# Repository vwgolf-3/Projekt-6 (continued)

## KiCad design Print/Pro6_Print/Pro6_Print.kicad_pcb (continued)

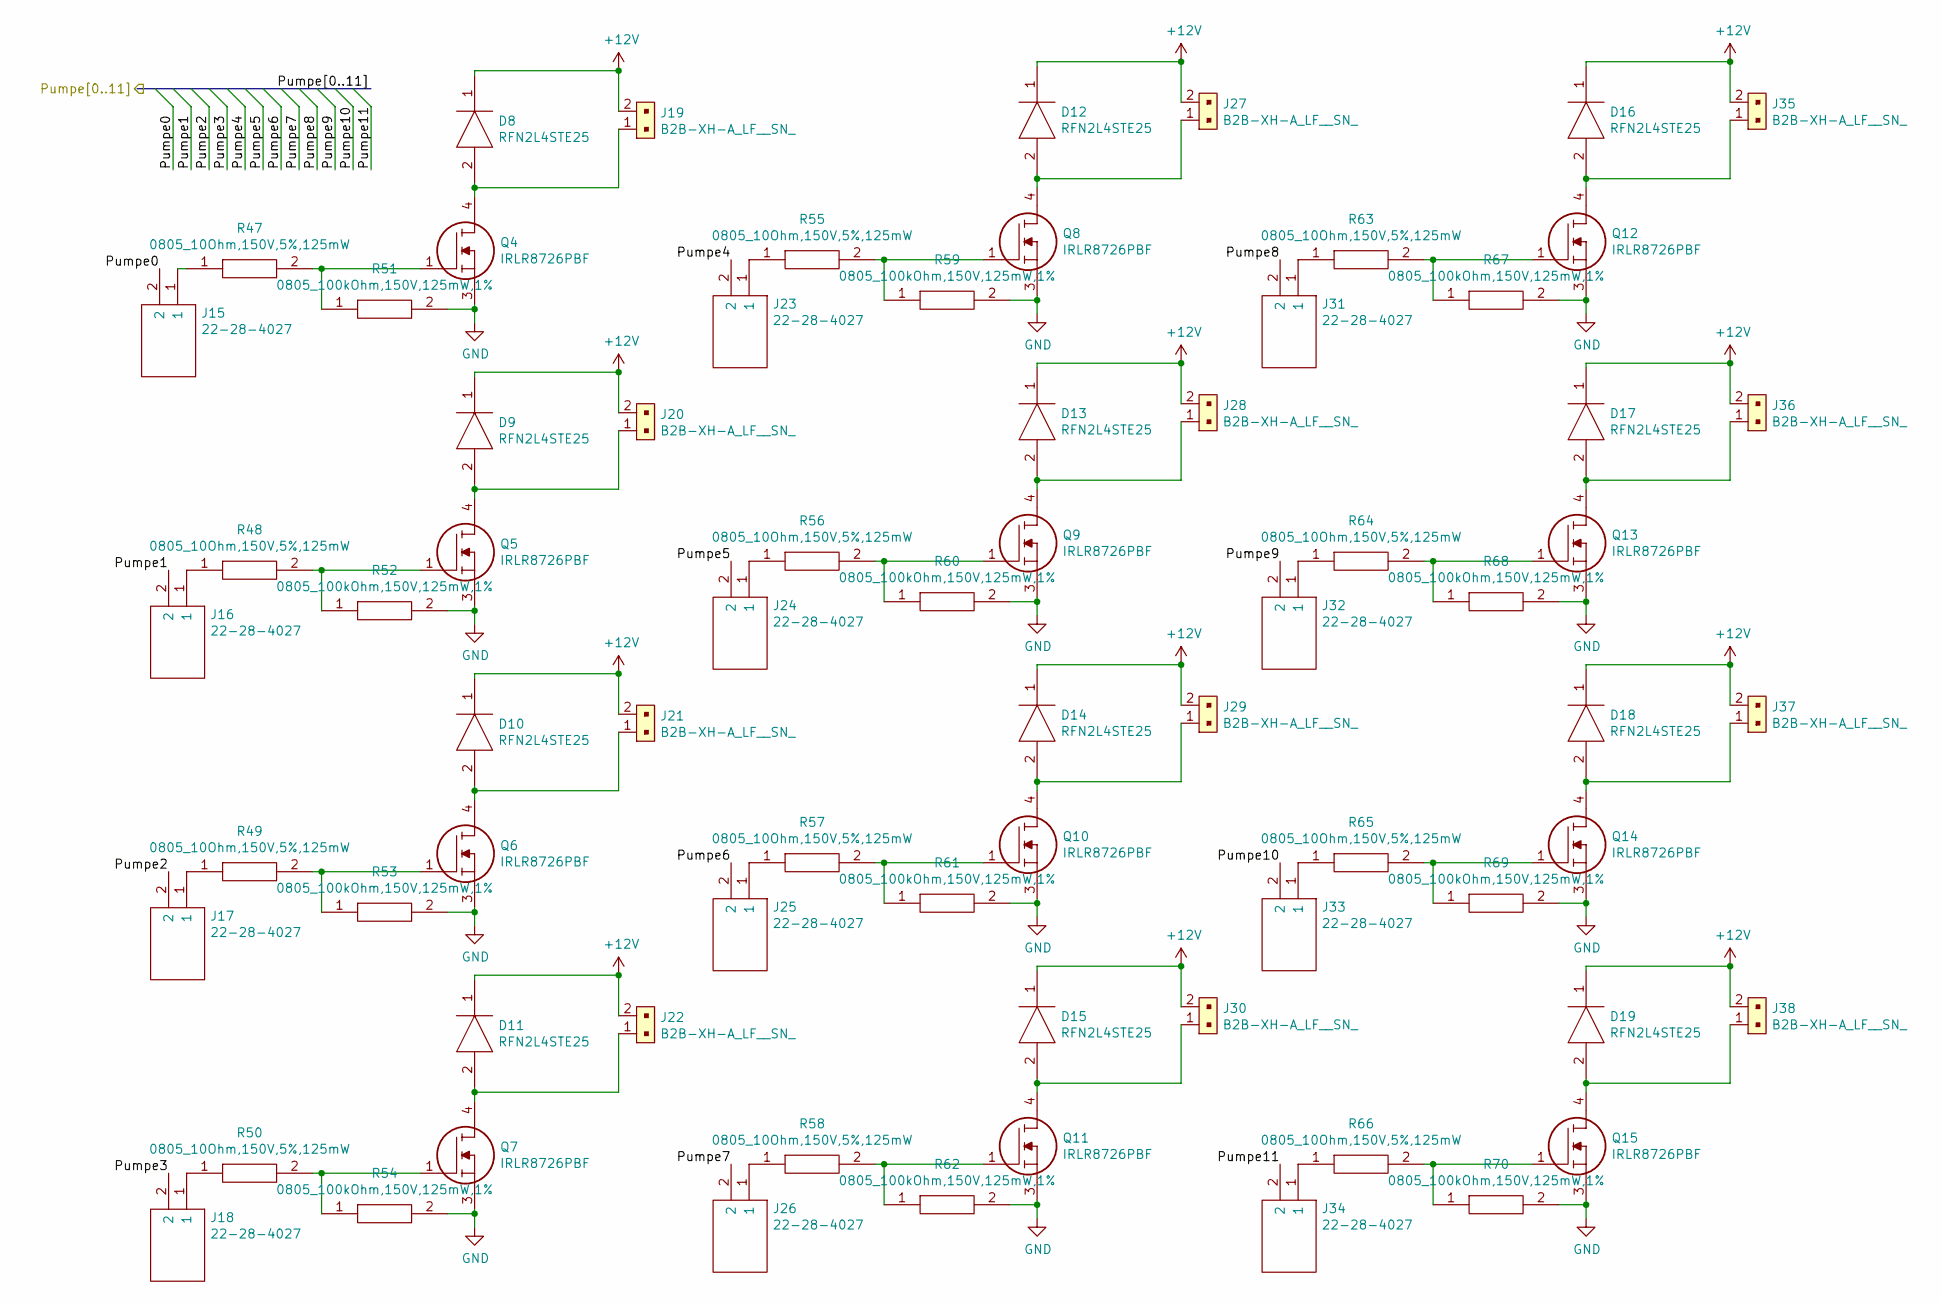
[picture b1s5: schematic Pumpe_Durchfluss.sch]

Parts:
D8, D9, D10, D11, D12, D13, D14, D15, D16, D17, D18, D19: RFN2L4STE25; DIOM5026X220N; Mouser Part Number 755-RFN2L4STE25
J15, J16, J17, J18, J23, J24, J25, J26, J31, J32, J33, J34: 22-28-4027; HDRV2W66P0X254_1X2_508X249X1067P; Mouser Part Number 538-22-28-4027
J19, J20, J21, J22, J27, J28, J29, J30, J35, J36, J37, J38: B2B-XH-A_LF__SN_; JST_XH_B2B-XH-A_1x02_P2.50mm_Vertical; MPN B2B-XH-A(LF)(SN); Digi-Key_PN 455-2247-ND
Q4, Q5, Q6, Q7, Q8, Q9, Q10, Q11, Q12, Q13, Q14, Q15: IRLR8726PBF; D-PAK_TO-252AA__1; Manufacturer_Part_Number IRLR8726PBF; Mouser Part Number 942-IRLR8726PBF
R47, R48, R49, R50, R55, R56, R57, R58, R63, R64, R65, R66: 0805_10Ohm,150V,5%,125mW; RESC2012X60N; Mouser Part Number 603-RC0805JR-1010RL
R51, R52, R53, R54, R59, R60, R61, R62, R67, R68, R69, R70: 0805_100kOhm,150V,125mW,1%; RESC2012X60N; Mouser Part Number 71-CRCW0805100KFKEAC

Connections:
+12V: D8.1, D9.1, D10.1, D11.1, D12.1, D13.1, D14.1, D15.1, D16.1, D17.1, D18.1, D19.1, J19.2, J20.2, J21.2, J22.2, J27.2, J28.2, J29.2, J30.2, J35.2, J36.2, J37.2, J38.2; also elsewhere on the board
/Atmega2560/Pumpe0: J15.2; also elsewhere on the board
/Atmega2560/Pumpe1: J16.2; also elsewhere on the board
/Atmega2560/Pumpe2: J17.2; also elsewhere on the board
/Atmega2560/Pumpe3: J18.2; also elsewhere on the board
/Atmega2560/Pumpe4: J23.2; also elsewhere on the board
/Atmega2560/Pumpe5: J24.2; also elsewhere on the board
/Atmega2560/Pumpe6: J25.2; also elsewhere on the board
/Atmega2560/Pumpe7: J26.2; also elsewhere on the board
/Atmega2560/Pumpe8: J31.2; also elsewhere on the board
/Atmega2560/Pumpe9: J32.2; also elsewhere on the board
/Atmega2560/Pumpe10: J33.2; also elsewhere on the board
/Atmega2560/Pumpe11: J34.2; also elsewhere on the board
GND: Q4.3, Q5.3, Q6.3, Q7.3, Q8.3, Q9.3, Q10.3, Q11.3, Q12.3, Q13.3, Q14.3, Q15.3, R51.2, R52.2, R53.2, R54.2, R59.2, R60.2, R61.2, R62.2, R67.2, R68.2, R69.2, R70.2; also elsewhere on the board
unnamed: D8.2, J19.1, Q4.4
unnamed: D9.2, J20.1, Q5.4
unnamed: D10.2, J21.1, Q6.4
unnamed: D11.2, J22.1, Q7.4
unnamed: D12.2, J27.1, Q8.4
unnamed: D13.2, J28.1, Q9.4
unnamed: D14.2, J29.1, Q10.4
unnamed: D15.2, J30.1, Q11.4
unnamed: D16.2, J35.1, Q12.4
unnamed: D17.2, J36.1, Q13.4
unnamed: D18.2, J37.1, Q14.4
unnamed: D19.2, J38.1, Q15.4
unnamed: J15.1, R47.1
unnamed: J16.1, R48.1
unnamed: J17.1, R49.1
unnamed: J18.1, R50.1
unnamed: J23.1, R55.1
unnamed: J24.1, R56.1
unnamed: J25.1, R57.1
unnamed: J26.1, R58.1
unnamed: J31.1, R63.1
unnamed: J32.1, R64.1
unnamed: J33.1, R65.1
unnamed: J34.1, R66.1
unnamed: Q4.1, R47.2, R51.1
unnamed: Q5.1, R48.2, R52.1
unnamed: Q6.1, R49.2, R53.1
unnamed: Q7.1, R50.2, R54.1
unnamed: Q8.1, R55.2, R59.1
unnamed: Q9.1, R56.2, R60.1
unnamed: Q10.1, R57.2, R61.1
unnamed: Q11.1, R58.2, R62.1
unnamed: Q12.1, R63.2, R67.1
unnamed: Q13.1, R64.2, R68.1
unnamed: Q14.1, R65.2, R69.1
unnamed: Q15.1, R66.2, R70.1

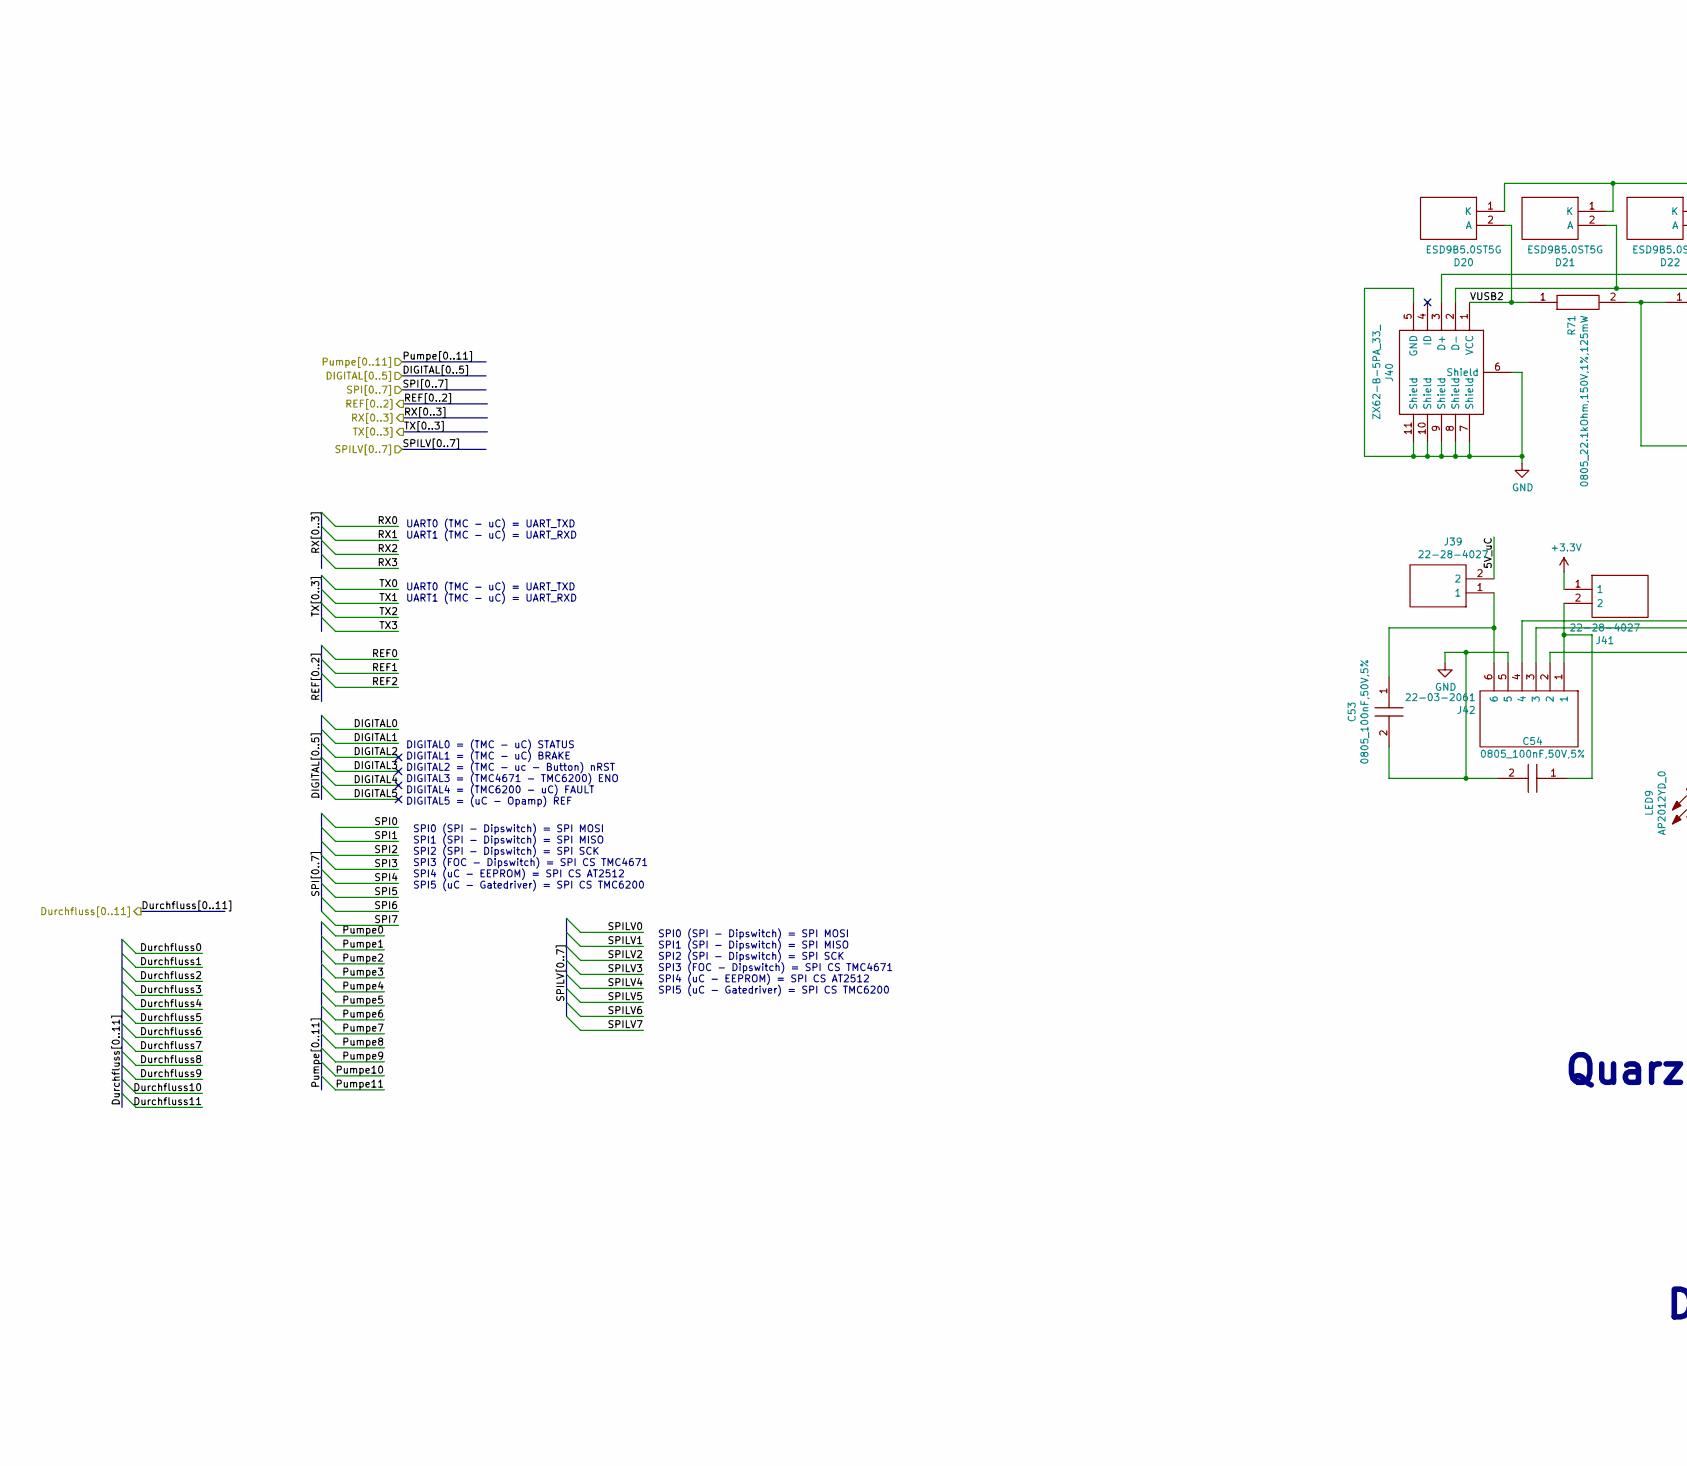
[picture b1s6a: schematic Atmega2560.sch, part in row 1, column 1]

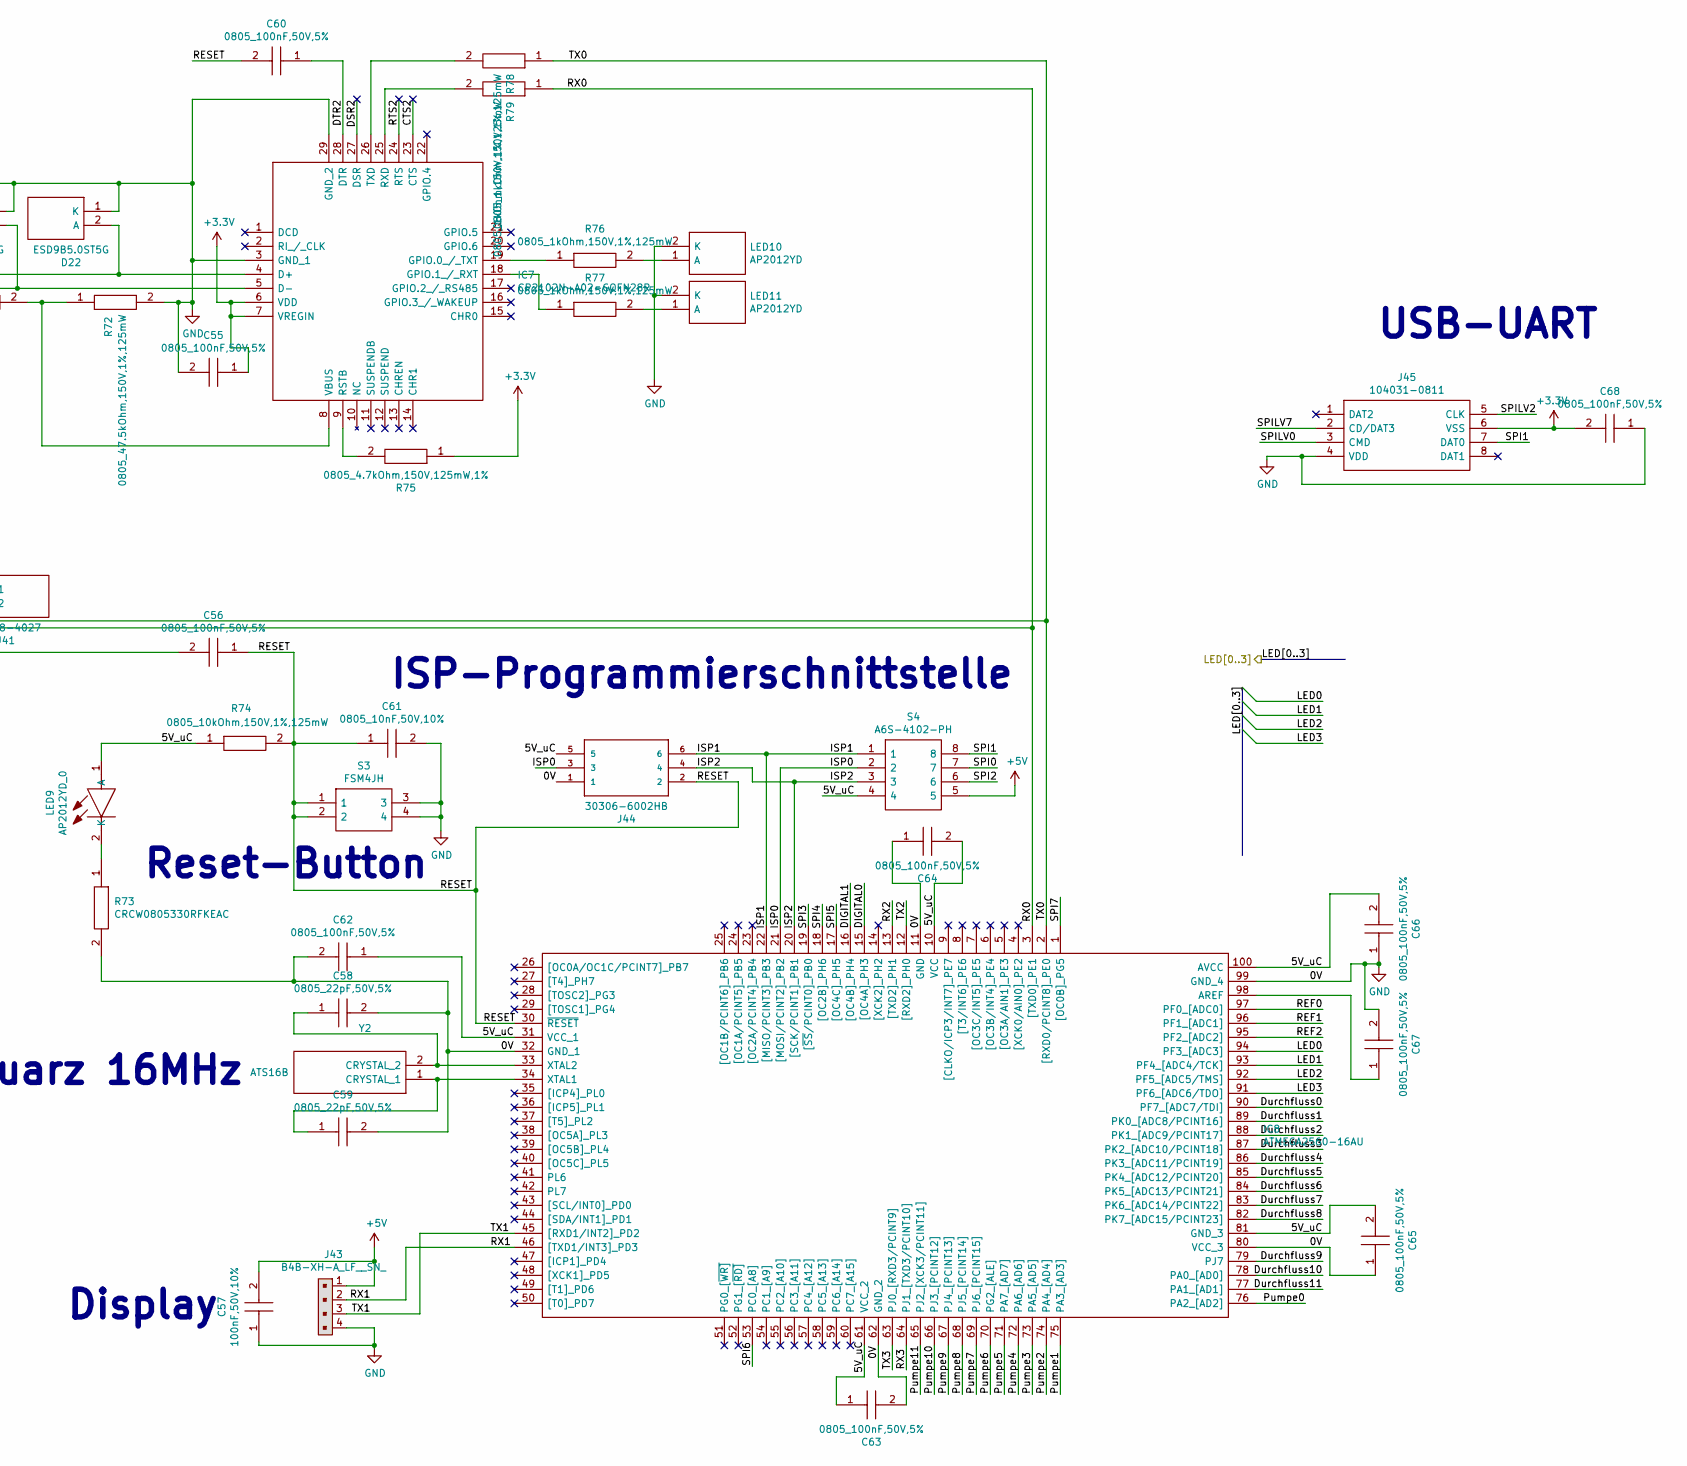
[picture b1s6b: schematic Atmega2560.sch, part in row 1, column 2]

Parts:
C53, C54, C55, C56, C60, C62, C63, C64, C65, C66, C67, C68: 0805_100nF,50V,5%; CAPC2012X88N; Mouser Part Number 80-C0805C104J5R
C57: 100nF,50V,10%; CAPC1608X95N; Manufacturer_Part_Number C0603C104K5RACTU; Mouser Part Number 80-C0603C104K5R
C58, C59: 0805_22pF,50V,5%; CAPC2012X70N; Mouser Part Number 710-885012007053
C61: 0805_10nF,50V,10%; CAPC2012X90N; Mouser Part Number 710-885012207092
D20, D21, D22: ESD9B5.0ST5G; SODFL1006X40N; Mouser Part Number 863-ESD9B5.0ST5G
IC7: CP2102N-A02-GQFN28R; QFN50P500X500X80-29N-D; Mouser Part Number 634-CP2102NA02QFN28R
IC8: ATMEGA2560-16AU; QFP50P1600X1600X120-100N; Mouser Part Number 556-ATMEGA2560-16AU
J39, J41: 22-28-4027; HDRV2W66P0X254_1X2_508X249X1067P; Mouser Part Number 538-22-28-4027
J40: ZX62-B-5PA_33_; ZX62B5PA33; Mouser Part Number 798-ZX62-B-5PA33
J42: 22-03-2061; HDRV6W82P0X254_1X6_1499X236X1117P; Mouser Part Number 538-22-03-2061
J43: B4B-XH-A_LF__SN_; PinHeader_1x4_P2.5mm_Drill1.1mm; MPN B4B-XH-A(LF)(SN); Digi-Key_PN 455-2249-ND
J44: 30306-6002HB; 3M_30306-6002HB
J45: 104031-0811; 1040310811; Mouser Part Number 538-104031-0811
LED9: AP2012YD_0; AP2012YD; Mouser Part Number 604-AP2012YD
LED10, LED11: AP2012YD; Mouser Part Number 604-AP2012YD
R71: 0805_22.1kOhm,150V,1%,125mW; RESC2012X70N; Mouser Part Number 667-ERJ-6ENF2212V
R72: 0805_47.5kOhm,150V,1%,125mW; RESC2012X50N; Mouser Part Number 71-CRCW0805-47.5K-E3
R73: CRCW0805330RFKEAC; RESC2012X60N; Mouser Part Number 71-CRCW0805330RFKEAC
R74: 0805_10kOhm,150V,1%,125mW; RESC2012X60N; Mouser Part Number 71-CRCW080510K0FKEAC
R75: 0805_4.7kOhm,150V,125mW,1%; RESC2012X70N; Mouser Part Number 667-ERJ-6ENF4701V
R76, R77, R78, R79: 0805_1kOhm,150V,1%,125mW; RESC2012X60N; Mouser Part Number 71-CRCW08051K00FKEAC
S3: FSM4JH; Mouser Part Number 506-FSM4JH
S4: A6S-4102-PH; SOP254P980X380-8N; Mouser Part Number 653-A6S-4102-PH
Y2: ATS16B; Mouser Part Number 774-ATS16B

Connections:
+3V3: C55.1, C68.2, IC7.6 (VDD), IC7.7 (VREGIN), J41.1, J45.6 (VSS), R75.1; also elsewhere on the board
+5V: C57.2, J43.1, S4.5; also elsewhere on the board
/Atmega2560/5V_uC: C62.1, C63.1, C64.2, C65.2, C66.2, IC8.10 (VCC), IC8.31 (VCC_1), IC8.61 (VCC_2), IC8.81 (GND_3), IC8.100 (AVCC), J39.2, J44.5, LED9.1 (A), R74.1, S4.4
/Atmega2560/DIGITAL0: IC8.15 ([OC4A]_PH3); also elsewhere on the board
/Atmega2560/DIGITAL1: IC8.16 ([OC4B]_PH4); also elsewhere on the board
/Atmega2560/DTR2: C60.1, IC7.28 (DTR)
/Atmega2560/Durchfluss0: IC8.90 (PF7_[ADC7/TDI]); also elsewhere on the board
/Atmega2560/Durchfluss1: IC8.89 (PK0_[ADC8/PCINT16]); also elsewhere on the board
/Atmega2560/Durchfluss2: IC8.88 (PK1_[ADC9/PCINT17]); also elsewhere on the board
/Atmega2560/Durchfluss3: IC8.87 (PK2_[ADC10/PCINT18]); also elsewhere on the board
/Atmega2560/Durchfluss4: IC8.86 (PK3_[ADC11/PCINT19]); also elsewhere on the board
/Atmega2560/Durchfluss5: IC8.85 (PK4_[ADC12/PCINT20]); also elsewhere on the board
/Atmega2560/Durchfluss6: IC8.84 (PK5_[ADC13/PCINT21]); also elsewhere on the board
/Atmega2560/Durchfluss7: IC8.83 (PK6_[ADC14/PCINT22]); also elsewhere on the board
/Atmega2560/Durchfluss8: IC8.82 (PK7_[ADC15/PCINT23]); also elsewhere on the board
/Atmega2560/Durchfluss9: IC8.79 (PJ7); also elsewhere on the board
/Atmega2560/Durchfluss10: IC8.78 (PA0_[AD0]); also elsewhere on the board
/Atmega2560/Durchfluss11: IC8.77 (PA1_[AD1]); also elsewhere on the board
/Atmega2560/ISP0: IC8.21 ([MOSI/PCINT2]_PB2), J44.3, S4.2
/Atmega2560/ISP1: IC8.22 ([MISO/PCINT3]_PB3), J44.6, S4.1
/Atmega2560/ISP2: IC8.20 ([SCK/PCINT1]_PB1), J44.4, S4.3
/Atmega2560/LED0: IC8.94 (PF3_[ADC3]); also elsewhere on the board
/Atmega2560/LED1: IC8.93 (PF4_[ADC4/TCK]); also elsewhere on the board
/Atmega2560/LED2: IC8.92 (PF5_[ADC5/TMS]); also elsewhere on the board
/Atmega2560/LED3: IC8.91 (PF6_[ADC6/TDO]); also elsewhere on the board
/Atmega2560/Pumpe0: IC8.76 (PA2_[AD2]); also elsewhere on the board
/Atmega2560/Pumpe1: IC8.75 (PA3_[AD3]); also elsewhere on the board
/Atmega2560/Pumpe2: IC8.74 (PA4_[AD4]); also elsewhere on the board
/Atmega2560/Pumpe3: IC8.73 (PA5_[AD5]); also elsewhere on the board
/Atmega2560/Pumpe4: IC8.72 (PA6_[AD6]); also elsewhere on the board
/Atmega2560/Pumpe5: IC8.71 (PA7_[AD7]); also elsewhere on the board
/Atmega2560/Pumpe6: IC8.70 (PG2_[ALE]); also elsewhere on the board
/Atmega2560/Pumpe7: IC8.69 (PJ6_[PCINT15]); also elsewhere on the board
/Atmega2560/Pumpe8: IC8.68 (PJ5_[PCINT14]); also elsewhere on the board
/Atmega2560/Pumpe9: IC8.67 (PJ4_[PCINT13]); also elsewhere on the board
/Atmega2560/Pumpe10: IC8.66 (PJ3_[PCINT12]); also elsewhere on the board
/Atmega2560/Pumpe11: IC8.65 (PJ2_[XCK3/PCINT11]); also elsewhere on the board
/Atmega2560/REF0: IC8.97 (PF0_[ADC0]); also elsewhere on the board
/Atmega2560/REF1: IC8.96 (PF1_[ADC1]); also elsewhere on the board
/Atmega2560/REF2: IC8.95 (PF2_[ADC2]); also elsewhere on the board
/Atmega2560/RESET: C56.1, C60.2, C61.1, IC8.30 (~RESET), J44.2, R74.2, S3.1, S3.2
/Atmega2560/RX0: IC8.3 ([TXD0]_PE1), J42.3, R79.1
/Atmega2560/RX1: IC8.46 ([TXD1/INT3]_PD3), J43.2
/Atmega2560/RX2: IC8.13 ([TXD2]_PH1); also elsewhere on the board
/Atmega2560/RX3: IC8.64 (PJ1_[TXD3/PCINT10]); also elsewhere on the board
/Atmega2560/SPI0: S4.7; also elsewhere on the board
/Atmega2560/SPI1: J45.7 (DAT0), S4.8; also elsewhere on the board
/Atmega2560/SPI2: S4.6; also elsewhere on the board
/Atmega2560/SPI3: IC8.19 ([~SS~/PCINT0]_PB0); also elsewhere on the board
/Atmega2560/SPI4: IC8.18 ([OC2B]_PH6); also elsewhere on the board
/Atmega2560/SPI5: IC8.17 ([OC4C]_PH5); also elsewhere on the board
/Atmega2560/SPI6: IC8.53 (PC0_[A8]); also elsewhere on the board
/Atmega2560/SPI7: IC8.1 ([OC0B]_PG5); also elsewhere on the board
/Atmega2560/SPILV0: J45.3 (CMD); also elsewhere on the board
/Atmega2560/SPILV2: J45.5 (CLK); also elsewhere on the board
/Atmega2560/SPILV7: J45.2 (CD/DAT3); also elsewhere on the board
/Atmega2560/TX0: IC8.2 ([RXD0/PCINT8]_PE0), J42.4, R78.1
/Atmega2560/TX1: IC8.45 ([RXD1/INT2]_PD2), J43.3
/Atmega2560/TX2: IC8.12 ([RXD2]_PH0); also elsewhere on the board
/Atmega2560/TX3: IC8.63 (PJ0_[RXD3/PCINT9]); also elsewhere on the board
/Atmega2560/VUSB2: D20.2 (A), J40.1 (VCC), R71.1
GND: C53.2, C54.2, C55.2, C57.1, C58.2, C59.2, C61.2, C62.2, C63.2, C64.1, C65.1, C66.1, C67.2, C68.1, D20.1 (K), D21.1 (K), D22.1 (K), IC7.3 (GND_1), IC7.29 (GND_2), IC8.11 (GND), IC8.32 (GND_1), IC8.62 (GND_2), IC8.80 (VCC_3), IC8.99 (GND_4), J40.5 (GND), J40.6 (Shield), J40.7 (Shield), J40.8 (Shield), J40.9 (Shield), J40.10 (Shield), J40.11 (Shield), J42.5, J43.4, J44.1, J45.4 (VDD), LED10.2 (K), LED11.2 (K), R72.2, R73.2, S3.3, S3.4; also elsewhere on the board
unnamed: C53.1, J39.1, J42.6
unnamed: C54.1, J41.2, J42.1
unnamed: C56.2, J42.2
unnamed: C58.1, IC8.33 (XTAL2), Y2.2 (CRYSTAL_2)
unnamed: C59.1, IC8.34 (XTAL1), Y2.1 (CRYSTAL_1)
unnamed: C67.1, IC8.98 (AREF)
unnamed: D21.2 (A), IC7.5 (D-), J40.2 (D-)
unnamed: D22.2 (A), IC7.4 (D+), J40.3 (D+)
unnamed: IC7.8 (VBUS), R71.2, R72.1
unnamed: IC7.9 (RSTB), R75.2
unnamed: IC7.18 (GPIO.1_/_RXT), R77.1
unnamed: IC7.19 (GPIO.0_/_TXT), R76.1
unnamed: IC7.25 (RXD), R79.2
unnamed: IC7.26 (TXD), R78.2
unnamed: LED9.2 (K), R73.1
unnamed: LED10.1 (A), R76.2
unnamed: LED11.1 (A), R77.2

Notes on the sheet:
SPI0 (SPI - Dipswitch) = SPI MOSI SPI1 (SPI - Dipswitch) = SPI MISO SPI2 (SPI - Dipswitch) = SPI SCK SPI3 (FOC - Dipswitch) = SPI CS TMC4671 SPI4 (uC - EEPROM) = SPI CS AT2512 SPI5 (uC - Gatedriver) = SPI CS TMC6200
DIGITAL0 = (TMC - uC) STATUS DIGITAL1 = (TMC - uC) BRAKE DIGITAL2 = (TMC - uc - Button) nRST DIGITAL3 = (TMC4671 - TMC6200) ENO DIGITAL4 = (TMC6200 - uC) FAULT DIGITAL5 = (uC - Opamp) REF
UART0 (TMC - uC) = UART_TXD UART1 (TMC - uC) = UART_RXD
Display
ISP-Programmierschnittstelle
USB-UART
Quarz 16MHz
Reset-Button

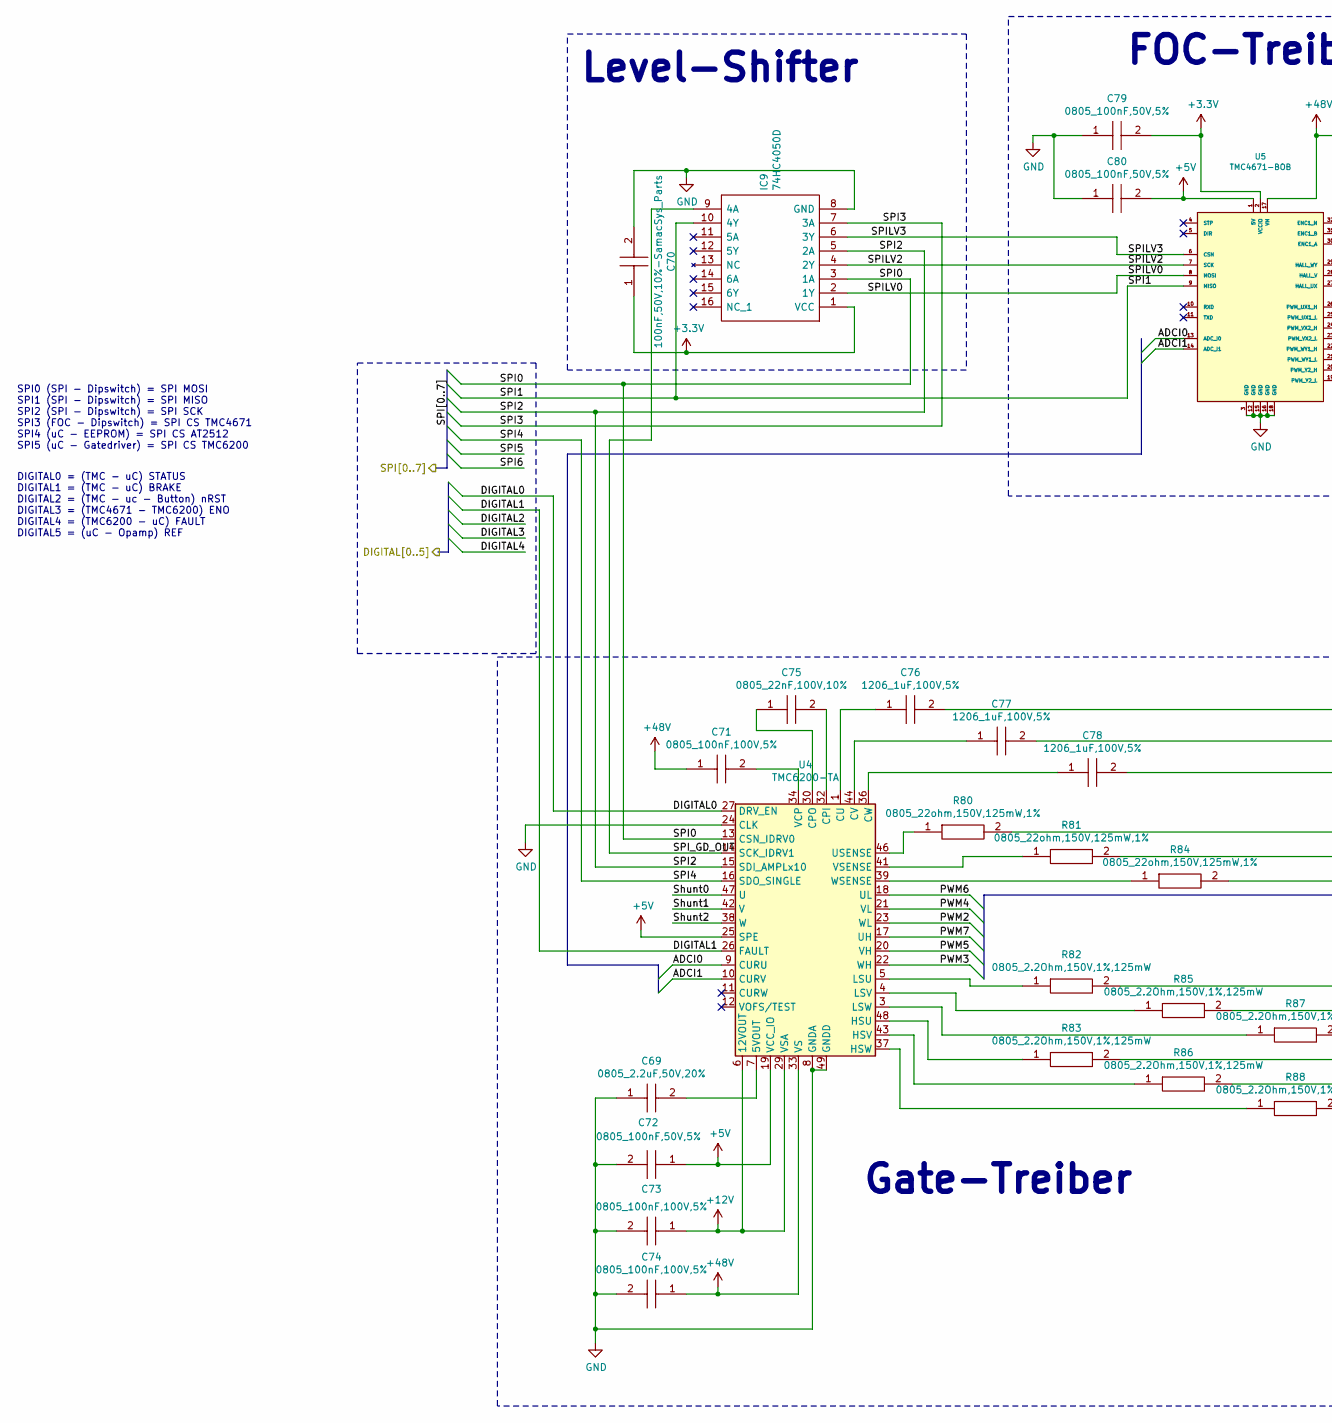
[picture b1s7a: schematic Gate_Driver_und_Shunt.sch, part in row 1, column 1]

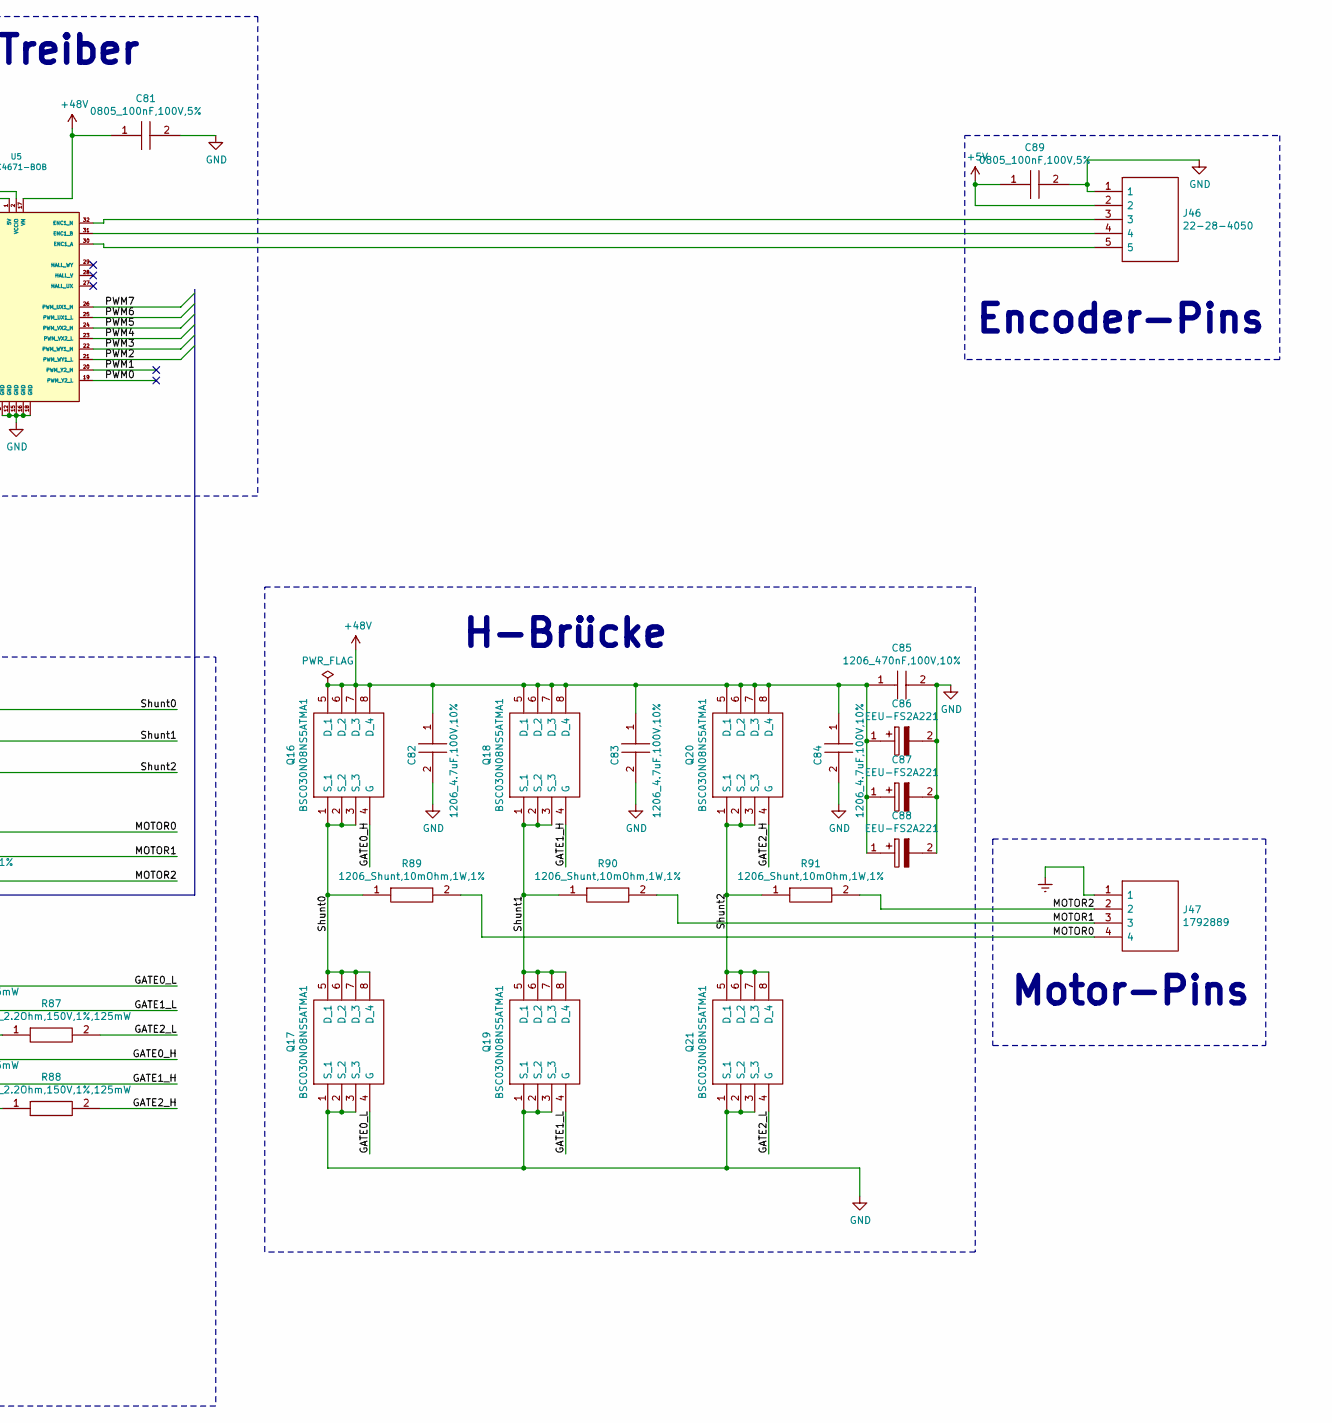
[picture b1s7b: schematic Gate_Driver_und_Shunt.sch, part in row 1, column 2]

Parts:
C69: 0805_2.2uF,50V,20%; CAPC2012X95N; Mouser Part Number 963-UMK212BB7225MG-T
C70: 100nF,50V,10%-SamacSys_Parts; CAPC1608X95N; Manufacturer_Part_Number C0603C104K5RACTU; Mouser Part Number 80-C0603C104K5R
C71, C73, C74, C81, C89: 0805_100nF,100V,5%; CAPC2012X140N; Mouser Part Number 581-08051C104JAT2A
C72, C79, C80: 0805_100nF,50V,5%; CAPC2012X88N; Mouser Part Number 80-C0805C104J5R
C75: 0805_22nF,100V,10%; CAPC2012X145N; Mouser Part Number 810-C2012X7R2A223K
C76, C77, C78: 1206_1uF,100V,5%; CAPC3316X185N; Mouser Part Number 80-C1206X105J1R
C82, C83, C84: 1206_4.7uF,100V,10%; CAPC3225X270N; Mouser Part Number 963-HMK325C7475KM-PE
C85: 1206_470nF,100V,10%; CAPC3216X175N; Mouser Part Number 80-C1206C474K1RAUTO
C86, C87, C88: EEU-FS2A221; CAPPRD500W65D1250H2700; Mouser Part Number 667-EEU-FS2A221
IC9: 74HC4050D; SOIC127P600X175-16N; Mouser Part Number 771-74HC4050D
J46: 22-28-4050; HDRV5W66P0X254_1X5_1270X249X838P; Mouser Part Number 538-22-28-4050
J47: 1792889; SHDR4W100P0X500_1X4_2000X1050X1360P; Mouser Part Number 651-1792889
Q16, Q17, Q18, Q19, Q20, Q21: BSC030N08NS5ATMA1; PG-TDSON-8-5; Mouser Part Number 726-BSC030N08NS5ATMA
R80, R81, R84: 0805_22ohm,150V,125mW,1%; RESC2012X70N; Mouser Part Number 667-ERJ-6ENF22R0V
R82, R83, R85, R86, R87, R88: 0805_2.2Ohm,150V,1%,125mW; RESC2012X50N; Mouser Part Number 71-CRCW08052R20FKEA
R89, R90, R91: 1206_Shunt,10mOhm,1W,1%; RESC3216X75N; Mouser Part Number 667-ERJ-8CWFR010V
U4: TMC6200-TA; TQFP-48-1EP_7x7mm_P0.5mm_EP5x5mm_ThermalVias
U5: TMC4671-BOB; 32pin1,5x1,6-BOB; MPN TMC4671-BOB; Digi-Key_PN 1460-1317-ND

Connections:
+3V3: C70.1, C79.2, IC9.1 (VCC), U5.2 (VCCIO); also elsewhere on the board
+5V: C72.1, C80.2, C89.1, J46.2, U4.19 (VCC_IO), U4.25 (SPE), U5.1 (5V); also elsewhere on the board
+12V: C73.1, U4.6 (12VOUT), U4.29 (VSA); also elsewhere on the board
+48V: C71.1, C74.1, C81.1, C82.1, C83.1, C84.1, C85.1, C86.1, C87.1, C88.1, Q16.5 (D_1), Q16.6 (D_2), Q16.7 (D_3), Q16.8 (D_4), Q16.9 (D_4), Q18.5 (D_1), Q18.6 (D_2), Q18.7 (D_3), Q18.8 (D_4), Q18.9 (D_4), Q20.5 (D_1), Q20.6 (D_2), Q20.7 (D_3), Q20.8 (D_4), Q20.9 (D_4), U4.33 (VS), U5.17 (VM); also elsewhere on the board
/Atmega2560/DIGITAL0: U4.27 (DRV_EN); also elsewhere on the board
/Atmega2560/DIGITAL1: U4.26 (FAULT); also elsewhere on the board
/Atmega2560/SPI0: IC9.3 (1A), U4.13 (CSN_IDRV0); also elsewhere on the board
/Atmega2560/SPI1: IC9.10 (4Y), U5.9 (MISO); also elsewhere on the board
/Atmega2560/SPI2: IC9.5 (2A), U4.15 (SDI_AMPLx10); also elsewhere on the board
/Atmega2560/SPI3: IC9.7 (3A); also elsewhere on the board
/Atmega2560/SPI4: U4.16 (SDO_SINGLE); also elsewhere on the board
/Gate_Driver_und_Shunt/ADCI0: U4.9 (CURU), U5.13 (ADC_I0)
/Gate_Driver_und_Shunt/ADCI1: U4.10 (CURV), U5.14 (ADC_I1)
/Gate_Driver_und_Shunt/GATE0_H: Q16.4 (G), R83.2
/Gate_Driver_und_Shunt/GATE0_L: Q17.4 (G), R82.2
/Gate_Driver_und_Shunt/GATE1_H: Q18.4 (G), R86.2
/Gate_Driver_und_Shunt/GATE1_L: Q19.4 (G), R85.2
/Gate_Driver_und_Shunt/GATE2_H: Q20.4 (G), R88.2
/Gate_Driver_und_Shunt/GATE2_L: Q21.4 (G), R87.2
/Gate_Driver_und_Shunt/MOTOR0: J47.4, R80.2, R89.2
/Gate_Driver_und_Shunt/MOTOR1: J47.3, R81.2, R90.2
/Gate_Driver_und_Shunt/MOTOR2: J47.2, R84.2, R91.2
/Gate_Driver_und_Shunt/PWM2: U4.23 (WL), U5.21 (PWM_WY1_L)
/Gate_Driver_und_Shunt/PWM3: U4.22 (WH), U5.22 (PWM_WY1_H)
/Gate_Driver_und_Shunt/PWM4: U4.21 (VL), U5.23 (PWM_VX2_L)
/Gate_Driver_und_Shunt/PWM5: U4.20 (VH), U5.24 (PWM_VX2_H)
/Gate_Driver_und_Shunt/PWM6: U4.18 (UL), U5.25 (PWM_UX1_L)
/Gate_Driver_und_Shunt/PWM7: U4.17 (UH), U5.26 (PWM_UX1_H)
/Gate_Driver_und_Shunt/SPILV0: IC9.2 (1Y), U5.8 (MOSI)
/Gate_Driver_und_Shunt/SPILV2: IC9.4 (2Y), U5.7 (SCK)
/Gate_Driver_und_Shunt/SPILV3: IC9.6 (3Y), U5.6 (CSN)
/Gate_Driver_und_Shunt/SPI_GD_OUT: IC9.9 (4A), U4.14 (SCK_IDRV1)
/Gate_Driver_und_Shunt/Shunt0: C76.2, Q16.1 (S_1), Q16.2 (S_2), Q16.3 (S_3), Q17.5 (D_1), Q17.6 (D_2), Q17.7 (D_3), Q17.8 (D_4), Q17.9 (D_4), R89.1, U4.47 (U)
/Gate_Driver_und_Shunt/Shunt1: C77.2, Q18.1 (S_1), Q18.2 (S_2), Q18.3 (S_3), Q19.5 (D_1), Q19.6 (D_2), Q19.7 (D_3), Q19.8 (D_4), Q19.9 (D_4), R90.1, U4.42 (V)
/Gate_Driver_und_Shunt/Shunt2: C78.2, Q20.1 (S_1), Q20.2 (S_2), Q20.3 (S_3), Q21.5 (D_1), Q21.6 (D_2), Q21.7 (D_3), Q21.8 (D_4), Q21.9 (D_4), R91.1, U4.38 (W)
Earth: J47.1; also elsewhere on the board
GND: C69.1, C70.2, C72.2, C73.2, C74.2, C79.1, C80.1, C81.2, C82.2, C83.2, C84.2, C85.2, C86.2, C87.2, C88.2, C89.2, IC9.8 (GND), J46.1, Q17.1 (S_1), Q17.2 (S_2), Q17.3 (S_3), Q19.1 (S_1), Q19.2 (S_2), Q19.3 (S_3), Q21.1 (S_1), Q21.2 (S_2), Q21.3 (S_3), U4.8 (GNDA), U4.24 (CLK), U4.49 (GNDD), U5.3 (GND), U5.12 (GND), U5.15 (GND), U5.16 (GND), U5.18 (GND); also elsewhere on the board
unnamed: C69.2, U4.7 (5VOUT)
unnamed: C71.2, U4.34 (VCP)
unnamed: C75.1, U4.30 (CPO)
unnamed: C75.2, U4.32 (CPI)
unnamed: C76.1, U4.1 (CU)
unnamed: C77.1, U4.44 (CV)
unnamed: C78.1, U4.36 (CW)
unnamed: J46.3, U5.32 (ENC1_N)
unnamed: J46.4, U5.31 (ENC1_B)
unnamed: J46.5, U5.30 (ENC1_A)
unnamed: R80.1, U4.46 (USENSE)
unnamed: R81.1, U4.41 (VSENSE)
unnamed: R82.1, U4.5 (LSU)
unnamed: R83.1, U4.48 (HSU)
unnamed: R84.1, U4.39 (WSENSE)
unnamed: R85.1, U4.4 (LSV)
unnamed: R86.1, U4.43 (HSV)
unnamed: R87.1, U4.3 (LSW)
unnamed: R88.1, U4.37 (HSW)

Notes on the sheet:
DIGITAL0 = (TMC - uC) STATUS DIGITAL1 = (TMC - uC) BRAKE DIGITAL2 = (TMC - uc - Button) nRST DIGITAL3 = (TMC4671 - TMC6200) ENO DIGITAL4 = (TMC6200 - uC) FAULT DIGITAL5 = (uC - Opamp) REF
Gate-Treiber
FOC-Treiber
Level-Shifter
SPI0 (SPI - Dipswitch) = SPI MOSI SPI1 (SPI - Dipswitch) = SPI MISO SPI2 (SPI - Dipswitch) = SPI SCK SPI3 (FOC - Dipswitch) = SPI CS TMC4671 SPI4 (uC - EEPROM) = SPI CS AT2512 SPI5 (uC - Gatedriver) = SPI CS TMC6200
H-Brücke
Motor-Pins
Encoder-Pins
